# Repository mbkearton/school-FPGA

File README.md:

"# school-FPGA" 
"# school-FPGA"

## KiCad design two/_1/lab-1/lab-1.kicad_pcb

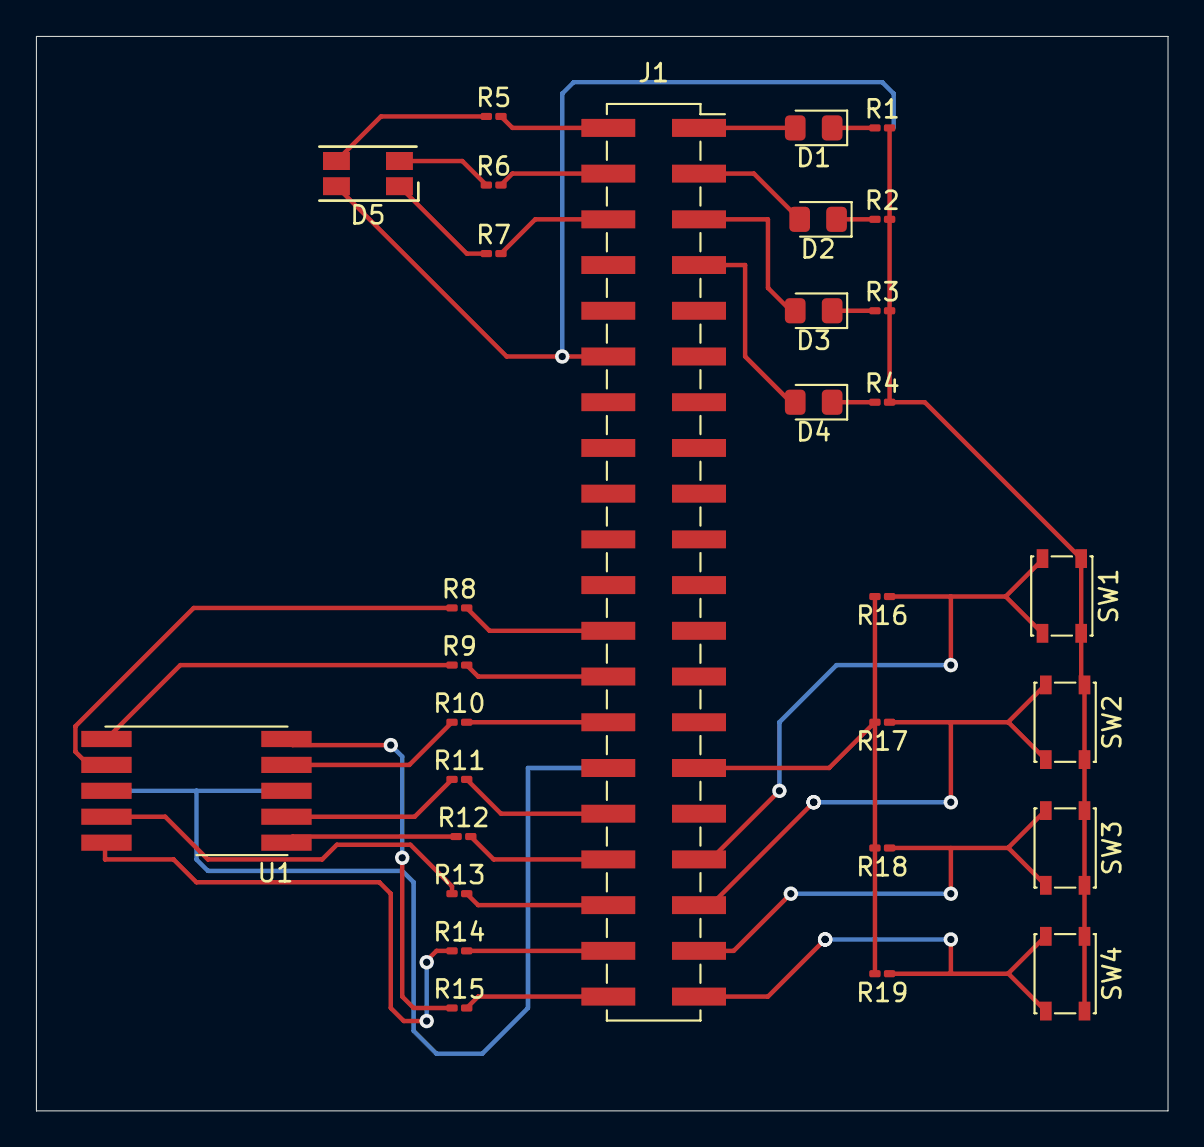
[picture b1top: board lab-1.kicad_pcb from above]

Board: 2 copper layers, 62.9 x 59.7 mm, 30 parts (0 on the bottom side), 36 nets.

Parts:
D1, D2, D3, D4: LED; LED_0805_2012Metric_Pad1.15x1.40mm_HandSolder
D5: LED_RGBC; LED_RGB_1210
J1: Conn_02x20_Odd_Even; PinSocket_2x20_P2.54mm_Vertical_SMD
R1, R2, R3, R4: 200; R_0201_0603Metric_Pad0.64x0.40mm_HandSolder
R5, R6, R7: 150; R_0201_0603Metric_Pad0.64x0.40mm_HandSolder
R8, R9, R10, R11, R12, R13, R14, R15: 100; R_0201_0603Metric_Pad0.64x0.40mm_HandSolder
R16, R17, R18, R19: 10K; R_0201_0603Metric_Pad0.64x0.40mm_HandSolder
SW1, SW2, SW3, SW4: SW_Push; SW_SPST_PTS810
U1: KCSC02-106

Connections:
+3V3: J1.29, R16.2, R17.2, R18.2, R19.2
GND: D5.4, J1.12, J1.30, R1.2, R2.2, R3.2, R4.2, SW1.1, SW2.1, SW3.1, SW4.1, U1.3, U1.8
unnamed: D1.1, R1.1
unnamed: D1.2, J1.1
unnamed: D2.1, R2.1
unnamed: D2.2, J1.3
unnamed: D3.1, R3.1
unnamed: D3.2, J1.5
unnamed: D4.1, R4.1
unnamed: D4.2, J1.7
unnamed: D5.1, R7.1
unnamed: D5.2, R6.1
unnamed: D5.3, R5.1
unnamed: J1.2, R5.2
unnamed: J1.4, R6.2
unnamed: J1.6, R7.2
unnamed: J1.24, R8.2
unnamed: J1.26, R9.2
unnamed: J1.28, R10.2
unnamed: J1.32, R11.2
unnamed: J1.33, R16.1, SW1.2
unnamed: J1.34, R12.2
unnamed: J1.35, R17.1, SW2.2
unnamed: J1.36, R13.2
unnamed: J1.37, R18.1, SW3.2
unnamed: J1.38, R14.2
unnamed: J1.39, R19.1, SW4.2
unnamed: J1.40, R15.2
unnamed: R8.1, U1.7
unnamed: R9.1, U1.6
unnamed: R10.1, U1.4
unnamed: R11.1, U1.2
unnamed: R12.1, U1.1
unnamed: R13.1, U1.9
unnamed: R14.1, U1.10
unnamed: R15.1, U1.5

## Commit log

2022-03-28 Added .gitignore
2022-03-28 Added work from CST-133
2022-03-28 Added work from CST-231
